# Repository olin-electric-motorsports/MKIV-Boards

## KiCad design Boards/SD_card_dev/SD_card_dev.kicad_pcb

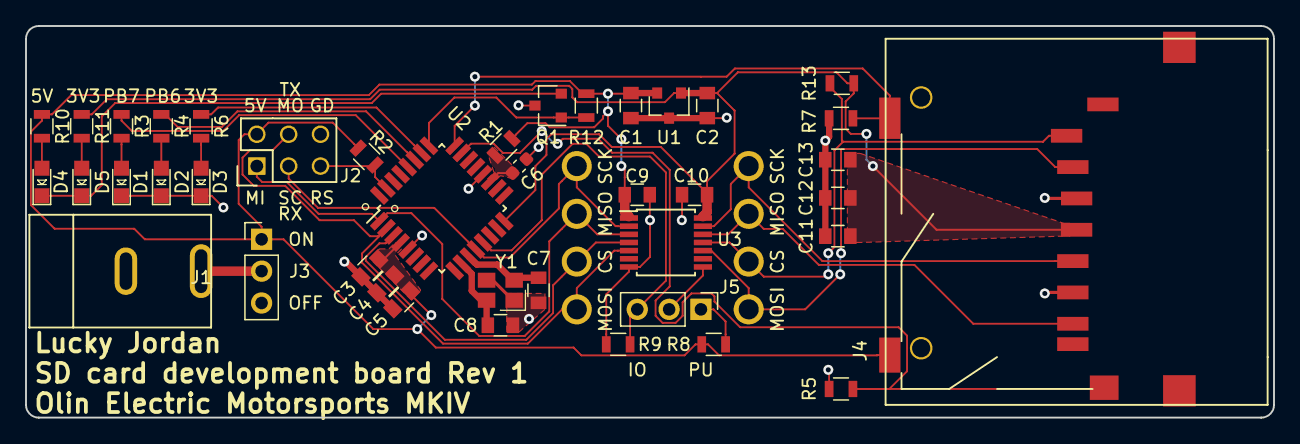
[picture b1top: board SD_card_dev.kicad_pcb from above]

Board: 2 copper layers, 99.6 x 31.2 mm, 49 parts (0 on the bottom side), 31 nets.

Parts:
C1, C2, C5, C9, C10, C13: C_0.1uF; C_0805_OEM
C3, C11: C_10uF; C_0805_OEM
C4, C12: C_1uF; C_0805_OEM
C6: C_100nF; C_0603_1608Metric
C7, C8: C_30pF; C_0805_OEM
CS: TP; tp_1.6mm
CS#2: TP; tp_1.6mm
D1, D2, D3, D4, D5: LED_0805; LED_0805_OEM
J1: Barrel_jack; barrel_jack_PJ-037A
J2: CONN_02X03; Pin_Header_Straight_2x03
J3, J5: CONN_01X03; Pin_Header_Straight_1x03_Pitch2.54mm
J4: SD_socket; sd_socket_molex_5009980900
MISO: TP; tp_1.6mm
MISO#2: TP; tp_1.6mm
MOSI: TP; tp_1.6mm
MOSI#2: TP; tp_1.6mm
Q1: SSM3K333R; SOT-23F
R1, R11: R_100; R_0805_OEM
R2, R5, R7, R8, R9, R12, R13: R_10K; R_0805_OEM
R3, R4, R6, R10: R_200; R_0805_OEM
SCK: TP; tp_1.6mm
SCK#2: TP; tp_1.6mm
U1: LM3480; SOT-23
U2: ATMEGA16M1; TQFP-32_7x7mm_Pitch0.8mm
U3: TXB0104; TSSOP-14_4.4x5mm_Pitch0.65mm
Y1: Crystal_SMD; Crystal_SMD_FA238

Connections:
+3V3: C2.1, C10.1, C11.1, C12.1, C13.1, J4.4, R11.1, R13.1, U1.1, U2.16, U3.14
+5V: C1.1, C3.1, C4.1, C5.1, C9.1, J2.2, J3.1, J4.10, R1.1, R2.1, R8.1, R10.1, R12.1, U1.2, U2.4, U3.1
/AVCC: C6.1, R1.2, U2.19
/Detect: J4.12, R7.1, U2.24
/LED1: R3.1, U2.28
/LED2: R4.1, U2.27
/LED3: R6.1, U2.26
/LED_drive: Q1.1, R12.2, U2.25
/MISO: J2.1, MISO.1, U2.1, U3.3
/MISO_3V3: J4.7, MISO#2.1, U3.12
/MOSI: J2.4, MOSI.1, U2.2, U3.5
/MOSI_3v3: J4.2, MOSI#2.1, U3.10
/OE: J5.2, U3.8
/OE_IO: J5.3, R9.1, U2.13
/Protect: J4.11, R5.1, U2.23
/RESET: J2.5, R2.2, U2.31
/SCK: J2.3, SCK.1, U2.12, U3.2
/SCK_3V3: J4.5, SCK#2.1, U3.13
/SS: CS.1, U2.3, U3.4
/SS_3V3: CS#2.1, J4.1, R13.2, U3.11
/XTAL1: C8.1, U2.10, Y1.3
/XTAL2: C7.1, U2.11, Y1.1
/cathode: D4.1, D5.1, Q1.2
GND: C1.2, C2.2, C3.2, C4.2, C5.2, C6.2, C7.2, C8.2, C9.2, C10.2, C11.2, C12.2, C13.2, D1.1, D2.1, D3.1, J1.2, J2.6, J4.3, J4.6, Q1.3, R5.2, R7.2, R9.2, U1.3, U2.5, U2.20, U3.7, Y1.2, Y1.4
unnamed: D1.2, R3.2
unnamed: D2.2, R4.2
unnamed: D3.2, R6.2
unnamed: D4.2, R10.2
unnamed: D5.2, R11.2
unnamed: J1.1, J3.2
unnamed: J5.1, R8.2

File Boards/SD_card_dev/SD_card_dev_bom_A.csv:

Component,Description,Part,References,Value,Footprint,Quantity Per PCB,Quantity Needed,Datasheet,MPN,MFN,PurchasingLink
1,"Capacitor, 0.1uF, 50V, 5%, 0805",C_0.1uF,C1 C2 C5 C9 C10 C13,C_0.1uF,C_0805_OEM,6,12,http://datasheets.avx.com/X7RDielectric.pdf,478-3352-1-ND,DK,https://www.digikey.com/products/en?keywords=478-3352-1-ND
2,"Capacitor, 0.1uF, 25V, 10%, 0603",C_100nF,C6,C_100nF,C_0603_1608Metric,1,2,http://www.samsungsem.com/kr/support/product-search/mlcc/CL1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,1276-6717-1-ND,DK,https://www.digikey.com/product-detail/en/samsung-electro-me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
3,"Capacitor, 10uF, 10V, 10%, 0805",C_10uF,C3 C11,C_10uF,C_0805_OEM,2,4,http://www.samsungsem.com/kr/support/product-search/mlcc/__i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,1276-1052-1-ND,DK,https://www.digikey.com/product-detail/en/samsung-electro-me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
4,"Capacitor, 1uF, 25V, 10%, 0805",C_1uF,C4 C12,C_1uF,C_0805_OEM,2,4,http://www.samsungsem.com/kr/support/product-search/mlcc/__i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,1276-2887-1-ND,DK,https://www.digikey.com/product-detail/en/samsung-electro-me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
5,"Capacitor, 30pF, 50V, 5%, 0805",C_30pF,C7 C8,C_30pF,C_0805_OEM,2,4,https://media.digikey.com/pdf/Data%20Sheets/Samsung%20PDFs/C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,1276-1130-1-ND,DK,https://www.digikey.com/product-detail/en/samsung-electro-me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
6,"LED, Green, 2.2V, 20mA, 0805",LED_0805,D1 D2 D3 D4 D5,LED_0805,LED_0805_OEM,5,10,http://www.osram-os.com/Graphics/XPic9/00078860_0.pdf,475-1410-1-ND,DK,https://www.digikey.com/products/en?keywords=475-1410-1-ND
7,"Barrel jack, 2.1x5.5mm, right angle, through hole",Barrel_jack,J1,Barrel_jack,barrel_jack_PJ-037A,1,2,https://www.cui.com/product/resource/pj-037a.pdf,CP-037A-ND,DK,https://www.digikey.com/product-detail/en/cui-inc/PJ-037A/CP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
8,"Connector header through hole 1x3 0.100"" (2.54mm)",CONN_01X03,J3 J5,CONN_01X03,Pin_Header_Straight_1x03_Pitch2.54mm,2,4,https://www.mouser.com/datasheet/2/181/M20-999-1218971.pdf,855-M20-9990346,Mouser,https://www.mouser.com/ProductDetail/Harwin/M20-9990346?qs=s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
9,"Connector header through hole 2x3 0.100"" (2.54mm)",CONN_02X03,J2,CONN_02X03,Pin_Header_Straight_2x03,1,2,http://portal.fciconnect.com/Comergent//fci/drawing/67996.pdf,609-3234-ND,DK,https://www.digikey.com/product-detail/en/amphenol-fci/67997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
10,SD card socket with detect switch,SD_socket,J4,SD_socket,sd_socket_molex_5009980900,1,2,https://www.molex.com/pdm_docs/sd/5009980900_sd.pdf,WM24032CT-ND,DK,https://www.digikey.com/product-detail/en/molex-llc/50099809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
11,"MOSFET, N-channel, 30V, 6A",SSM3K333R,Q1,SSM3K333R,SOT-23F,1,2,https://drive.google.com/drive/folders/0B-V-iZf33Y4GNzhDQTJZanJRbVk,SSM3K333RLFCT-ND,DK,https://www.digikey.com/product-detail/en/toshiba-semiconduc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
12,"Resistor, 100, 0.25W, 1%, 0805",R_100,R1 R11,R_100,R_0805_OEM,2,4,https://www.seielect.com/Catalog/SEI-rncp.pdf,RNCP0805FTD100RCT-ND,DK,https://www.digikey.com/products/en?keywords=RNCP0805FTD100RCT-ND
13,"Resistor, 10K, 0.25W, 1%, 0805",R_10K,R2 R5 R7 R8 R9 R12 R13,R_10K,R_0805_OEM,7,14,http://www.bourns.com/data/global/pdfs/CRS.pdf,CRS0805-FX-1002ELFCT-ND,DK,https://www.digikey.com/products/en?keywords=CRS0805-FX-1002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
14,"Resistor, 200, 0.125W, 5%, 0805",R_200,R3 R4 R6 R10,R_200,R_0805_OEM,4,8,https://www.seielect.com/Catalog/SEI-RMCF_RMCP.pdf,RMCF0805JT200RCT-ND,DK,https://www.digikey.com/products/en?keywords=RMCF0805JT200RCT-ND
15,"Microcontroller, 8-bit, 1KB RAM, 16KB Flash",ATMEGA16M1,U2,ATMEGA16M1,TQFP-32_7x7mm_Pitch0.8mm,1,2,http://ww1.microchip.com/downloads/en/DeviceDoc/Atmel-8209-8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,ATMEGA16M1-AU-ND,DK,https://www.digikey.com/product-detail/en/atmel/ATMEGA16M1-A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
16,"Linear regulator, 30V max input, 3.3V output, 100mA",LM3480,U1,LM3480,SOT-23,1,2,http://www.ti.com/lit/ds/symlink/lm3480.pdf,LM3480IM3-3.3CT-ND,DK,https://www.digikey.com/product-detail/en/texas-instruments/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
17,"Voltage level translator, 4-channel, bidirectional, TSSOP-14",TXB0104,U3,TXB0104,TSSOP-14_4.4x5mm_Pitch0.65mm,1,2,http://www.ti.com/lit/ds/symlink/txb0104.pdf,296-21929-1-ND,DK,https://www.digikey.com/product-detail/en/texas-instruments/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
18,CRYSTAL 16.0000MHZ 18PF SMD,Crystal_SMD,Y1,Crystal_SMD,Crystal_SMD_FA238,1,2,http://www.txccorp.com/download/products/quartz_crystals/201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,887-1125-1-ND,DK,https://www.digikey.com/product-detail/en/txc-corporation/7M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
,jumper,,,,,2,4,,S9341-ND,DK,https://www.digikey.com/product-detail/en/sullins-connector-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
,test point,,,,,8,16,,36-5006-ND,DK,
,wall wart,,,,,1,1,,993-1330-ND,DK,
,pocket avr programmer,,,,,1,1,,PGM-09825,sparkfun,https://www.sparkfun.com/products/9825
,uart to usb,,,,,1,1,,BOB-13830,sparkfun,https://www.sparkfun.com/products/13830
Component Groups:,18,,,,,,,,,,
Component Count:,41,,,,,,,,,,
Fitted Components:,41,,,,,,,,,,
Number of PCBs:,1,,,,,,,,,,
Total components:,41,,,,,,,,,,
Schematic Version:,A,,,,,,,,,,
Schematic Date:,2018-10-03,,,,,,,,,,
BoM Date:,Thu 04 Oct 2018 09:56:45 PM PDT,,,,,,,,,,
Schematic Source:,/home/lucky/Desktop/Formula/MKIV-Boards/Boards/SD_card_dev/SD_card_dev.sch,,,,,,,,,,
KiCad Version:,Eeschema 5.0.0-fee4fd1~66~ubuntu14.04.1,,,,,,,,,,

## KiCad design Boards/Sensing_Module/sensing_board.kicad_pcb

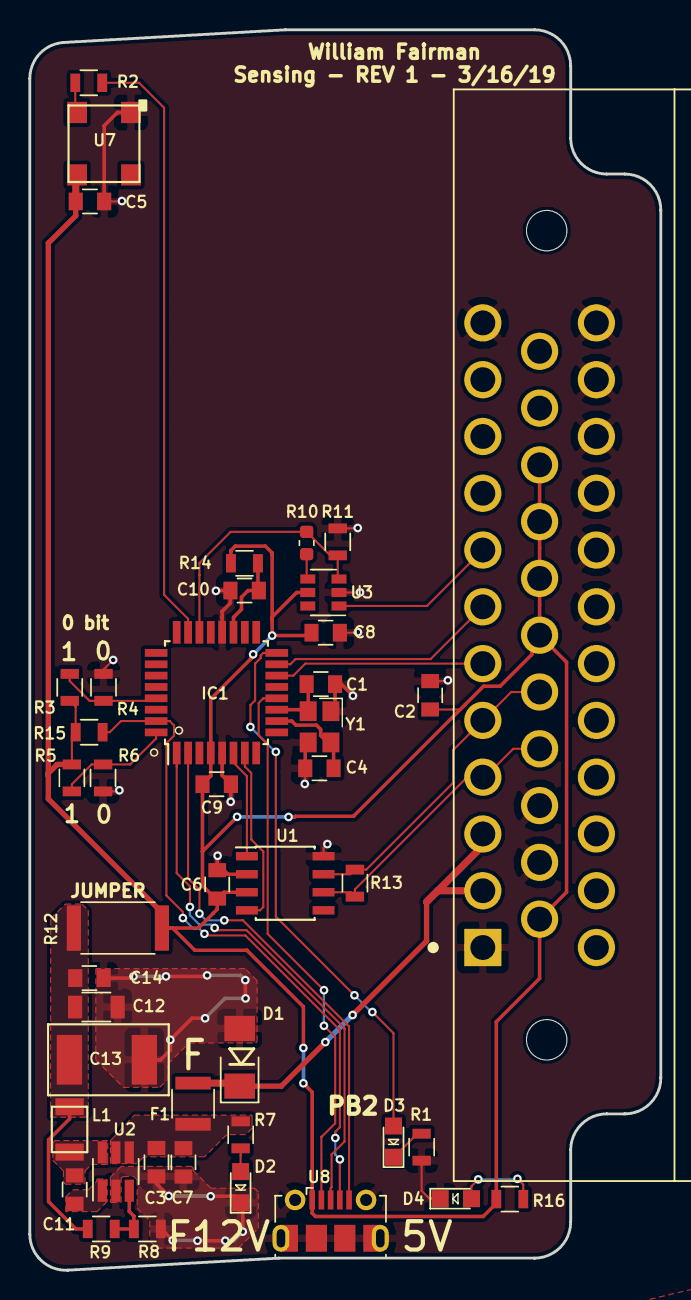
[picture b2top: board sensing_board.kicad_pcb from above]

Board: 2 copper layers, 44.5 x 87.4 mm, 44 parts (0 on the bottom side), 32 nets.

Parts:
C1, C4: C_30pF; C_0805_OEM
C2, C3, C5, C6, C8, C9, C11: C_0.1uF; C_0805_OEM
C7: C_2.2uF; C_0805_OEM
C10: C_100pF; C_0805_OEM
C12: C_22uF; C_1206_OEM
C13: C_33uF; C_1812
C14: C_47uF; C_0805_OEM
D1: D_Zener_18V; DO-214AA
D2, D3, D4: LED_0805; LED_0805_OEM
F1: F_500mA_16V; Fuse_1210
IC1: ATMEGA16M1; TQFP-32_7x7mm_Pitch0.8mm
J1: Ampseal_35_RA; TE_1-776180-1_35_RA
L1: L_100uH
R1, R2, R7, R16: R_200; R_0805_OEM
R3, R4, R5, R6, R11: R_1K; R_0805_OEM
R8: R_25K; R_0805_OEM
R9: R_100K; R_0805_OEM
R10: R_0; R_0603_1608Metric
R12: R_0_2512; R_2512_OEM
R13: R_120; R_0805_OEM
R14: R_100; R_0805_OEM
R15: R_10k; R_0805_OEM
U1: CAN_Transceiver; SOIC-8_3.9x4.9mm_Pitch1.27mm_OEM
U2: TPS560430YF; SOT-23-6_Handsoldering
U3: LMV341; SOT-23-6
U7: SK812; SK6812
U8: USB_MicroB; USB_Micro-B_Molex-105017-0001
Y1: Crystal_SMD; Crystal_SMD_FA238

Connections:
/12V: D1.1, F1.2, J1.2, J1.3
/BRAKETEMP: IC1.14, J1.6
/CANH: J1.5, J1.17, R13.1, U1.7
/CANL: J1.4, J1.16, R13.2, U1.6
/HSENSOR: IC1.15, J1.7
/MISO: IC1.1, U8.3
/MOSI: IC1.2, U8.5
/NEO_PIXEL: IC1.23, R2.1
/POT: J1.8, U3.1
/POT_SIGNAL: IC1.22, R10.2, R11.1, U3.3
/P_LED_1: D3.2, IC1.16
/RESET: IC1.31, R15.2, U8.4
/RXCAN: IC1.7, U1.4
/SCK: IC1.12, U8.2
/TXCAN: IC1.6, U1.1
GND: C1.2, C2.1, C3.2, C4.2, C5.1, C6.2, C7.2, C8.2, C9.2, C10.2, C12.2, C13.2, C14.2, D1.2, D2.1, D4.1, IC1.5, IC1.20, J1.1, J1.12, J1.14, J1.15, J1.30, J1.31, J1.32, J1.33, J1.34, J1.35, R1.2, R4.1, R6.2, R8.2, R11.2, U1.2, U1.8, U2.2, U3.2, U7.1, U8.6, Y1.2, Y1.4
unnamed: C1.1, IC1.11, Y1.1
unnamed: C3.1, C7.1, F1.1, R7.1, U2.4, U2.5
unnamed: C4.1, IC1.10, Y1.3
unnamed: C10.1, IC1.19, R14.2
unnamed: C11.1, U2.1
unnamed: C11.2, L1.1, U2.6
unnamed: C12.1, C13.1, C14.1, L1.2, R9.1, R12.2
unnamed: D2.2, R7.2
unnamed: D3.1, R1.1
unnamed: D4.2, R16.2
unnamed: IC1.29, R3.2, R4.2
unnamed: IC1.32, R5.2, R6.1
unnamed: R2.2, U7.2
unnamed: R8.1, R9.2, U2.3
unnamed: R10.1, U3.4
VCC: C2.2, C5.2, C6.1, C8.1, C9.1, IC1.4, J1.13, J1.18, J1.19, J1.20, J1.21, R3.1, R5.1, R12.1, R14.1, R15.1, R16.1, U1.3, U3.5, U7.3, U8.1

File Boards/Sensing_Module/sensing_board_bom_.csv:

Component,Description,Part,References,Value,Footprint,Quantity Per PCB,Datasheet,MFN,MPN,PurchasingLink,Package,Link,Digi-key Part Number,Purchasing Link
1,"b'Capacitor, 0.1uF, 50V, 5%, 0805'",b'C_0.1uF',b'C2 C3 C5 C6 C8 C9 C11',b'C_0.1uF',b'C_0805_OEM',b'7',b'http://datasheets.avx.com/X7RDielectric.pdf',b'DK Digi-Key',b'478-3352-1-ND',b'https://www.digikey.com/products/en?keywords=478-3352-1-ND',b'Value',b'',b'',b''
2,"b'Capacitor, 100pF, 50V, 5%, 0805'",b'C_100pF',b'C10',b'C_100pF',b'C_0805_OEM',b'1',b'https://content.kemet.com/datasheets/KEM_C1003_C0G_SMD.pdf',b'Digi-Key',b'399-1122-1-ND',b'https://www.digikey.com/product-detail/en/kemet/C0805C101J5G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,b'Value',b'',b'',b''
3,"b'Capacitor, 2.2uF, 10V, 10%, 0603'",b'C_2.2uF',b'C7',b'C_2.2uF',b'C_0603_1608Metric',b'1',b'http://www.yageo.com/documents/recent/UPY-GPHC_X5R_4V-to-50V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,b'DK',b'311-1451-1-ND',b'https://www.digikey.com/product-detail/en/yageo/CC0603KRX5R6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,b'',b'',b'',b''
4,"b'Capacitor, 22uF, 16V, 20%, 1206'",b'C_22uF',b'C12',b'C_22uF',b'C_1206_OEM',b'1',b'https://product.tdk.com/info/en/catalog/datasheets/mlcc_comm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,b'DK',b'445-11693-1-ND',b'https://www.digikey.com/product-detail/en/tdk-corporation/C3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,b'',b'',b'',b''
5,"b'Capacitor, 30pF, 50V, 5%, 0805'",b'C_30pF',b'C1 C4',b'C_30pF',b'C_0805_OEM',b'2',b'https://media.digikey.com/pdf/Data%20Sheets/Samsung%20PDFs/C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,b'Digi-Key',b'1276-1130-1-ND',b'https://www.digikey.com/product-detail/en/samsung-electro-me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,b'Value',b'',b'',b''
6,b'',b'C_33uF',b'C13',b'C_33uF',b'C_1812',b'1',b'https://product.tdk.com/info/en/catalog/datasheets/mlcc_comm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,b'C4532X7R1C336M250KC',b'445-3924-1-ND',b'https://www.digikey.com/product-detail/en/tdk-corporation/C4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,b'',b'',b'',b''
7,"b'Capacitor, 47uF, 6.3V, 20%, 0805'",b'C_47uF',b'C14',b'C_47uF',b'C_0805_OEM',b'1',b'http://www.samsungsem.com/kr/support/product-search/mlcc/__i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,b'DK',b'1276-6467-1-ND',b'https://www.digikey.com/product-detail/en/samsung-electro-me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,b'',b'',b'',b''
8,"b'Diode, Zener, 18V, 5W, 5%'",b'D_Zener_18V',b'D1',b'D_Zener_18V',b'DO-214AA',b'1',b'http://www.mccsemi.com/up_pdf/SMBJ5338B-SMBJ5388B(SMB).pdf',b'DK',b'SMBJ5355B-TPMSCT-ND',b'https://www.digikey.com/products/en?keywords=SMBJ5355B-TPMSCT-ND',b'',b'',b'',b''
9,"b'LED, Green, 2.2V, 20mA, 0805'",b'LED_0805',b'D2 D3 D4',b'LED_0805',b'LED_0805_OEM',b'3',b'http://www.osram-os.com/Graphics/XPic9/00078860_0.pdf',b'DK',b'475-1410-1-ND',b'https://www.digikey.com/products/en?keywords=475-1410-1-ND',b'',b'',b'',b''
10,"b'Fuse, PTC, 500mA, 16V, 1210'",b'F_500mA_16V',b'F1',b'F_500mA_16V',b'Fuse_1210',b'1',b'https://belfuse.com/resources/CircuitProtection/datasheets/0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,b'DK',b'507-1786-1-ND',b'https://www.digikey.com/product-detail/en/bel-fuse-inc/0ZCH0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,b'',b'',b'',b''
11,"b'Microcontroller, 8-bit, 1KB RAM, 16KB Flash'",b'ATMEGA16M1',b'IC1',b'ATMEGA16M1',b'TQFP-32_7x7mm_Pitch0.8mm',b'1',b'http://www.atmel.com/Images/Atmel-8209-8-bit%20AVR%20ATmega1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,b'Digi-Key',b'ATMEGA16M1-AU-ND',b'https://www.digikey.com/product-detail/en/atmel/ATMEGA16M1-A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,b'Value',b'',b'',b''
12,b'Ampseal connector 35 pin right angle',b'Ampseal_35_RA',b'J1',b'Ampseal_35_RA',b'TE_1-776180-1_35_RA',b'1',b'http://www.te.com/commerce/DocumentDelivery/DDEController?Ac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,b'TE',b'776180-1',b'http://www.te.com/usa-en/product-776180-1.html',b'',b'',b'',b''
13,b'',b'L_100uH',b'L1',b'L_100uH',b'L_100uH',b'1',b'https://product.tdk.com/info/en/catalog/datasheets/inductor_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,b'Digikey',b'445-15759-1-ND',b'',b'',b'https://www.digikey.com/product-detail/en/tdk-corporation/NL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,b'',b''
14,"b'Resistor, 0 ohm jumper, 0.1W, 0603'",b'R_0',b'R10',b'R_0',b'R_0603_1608Metric',b'1',b'http://industrial.panasonic.com/www-cgi/jvcr13pz.cgi?E+PZ+3+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,b'DK',b'P0.0GCT-ND',b'https://www.digikey.com/product-detail/en/panasonic-electron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,b'',b'',b'',b''
15,"b'Resistor, 0 ohm jumper, 3W, 2512'",b'R_0_2512',b'R12',b'R_0_2512',b'R_2512_OEM',b'1',b'http://www.te.com/commerce/DocumentDelivery/DDEController?Ac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,b'DK',b'A121322CT-ND',b'https://www.digikey.com/products/en?keywords=A121322CT-ND',b'',b'',b'',b''
16,"b'Resistor, 100, 0.25W, 1%, 0805'",b'R_100',b'R14',b'R_100',b'R_0805_OEM',b'1',b'https://www.seielect.com/Catalog/SEI-rncp.pdf',b'Digi-Key',b'RNCP0805FTD100RCT-ND',b'https://www.digikey.com/products/en?keywords=RNCP0805FTD100RCT-ND',b'Value',b'',b'',b''
17,"b'Resistor, 100K, 0.125W, 1%, 0805'",b'R_100K',b'R9',b'R_100K',b'R_0805_OEM',b'1',b'https://industrial.panasonic.com/cdbs/www-data/pdf/RDA0000/A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,b'DK',b'P100KCCT-ND',b'https://www.digikey.com/product-detail/en/panasonic-electron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,b'',b'',b'',b''
18,"b'Resistor, 10K, 0.25W, 1%, 0805'",b'R_10K',b'R15',b'R_10k',b'R_0805_OEM',b'1',b'http://www.bourns.com/data/global/pdfs/CRS.pdf',b'Digi-Key',b'CRS0805-FX-1002ELFCT-ND',b'https://www.digikey.com/products/en?keywords=CRS0805-FX-1002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,b'Value',b'',b'',b''
19,"b'Resistor, 120, 0.125W, 1%, 0805'",b'R_120',b'R13',b'R_120',b'R_0805_OEM',b'1',b'https://www.mouser.com/datasheet/2/315/AOA0000C304-1149620.pdf',b'DK',b'667-ERJ-6ENF1200V',b'https://www.mouser.com/ProductDetail/Panasonic-Industrial-De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,b'',b'',b'',b''
20,"b'Resistor, 1K, 0.25W, 1%, 0805'",b'R_1K',b'R3 R4 R5 R6 R11',b'R_1K',b'R_0805_OEM',b'5',b'https://www.seielect.com/Catalog/SEI-rncp.pdf',b'DK',b'RNCP0805FTD1K00CT-ND',b'https://www.digikey.com/products/en?keywords=RNCP0805FTD1K00CT-ND',b'',b'',b'',b''
21,"b'Resistor, 200, 0.125W, 5%, 0805'",b'R_200',b'R1 R2 R7 R16',b'R_200',b'R_0805_OEM',b'4',b'https://www.seielect.com/Catalog/SEI-RMCF_RMCP.pdf',b'DK',b'RMCF0805JT200RCT-ND',b'https://www.digikey.com/products/en?keywords=RMCF0805JT200RCT-ND',b'',b'',b'',b''
22,b'',b'R_25K',b'R8',b'R_25K',b'R_0805_OEM',b'1',b'https://www.te.com/commerce/DocumentDelivery/DDEController?A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,b'A124124CT-ND',b'',b'https://www.digikey.com/product-detail/en/te-connectivity-pa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,b'',b'',b'CPF-A-0805B25KE',b''
23,"b'High speed CAN transceiver, 1Mb/s'",b'MCP2561-E_SN',b'U1',b'CAN_Transceiver',b'SOIC-8_3.9x4.9mm_Pitch1.27mm_OEM',b'1',b'http://www.microchip.com/mymicrochip/filehandler.aspx?ddocna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,b'Digi-Key',b'MCP2561-E/SN-ND',b'https://www.digikey.com/products/en?keywords=mcp2561-e%2Fsn',b'Value',b'',b'',b''
24,"b'Op-amp, general purpose'",b'LMV341',b'U3',b'LMV341',b'SOT-23-6',b'1',b'http://www.ti.com/lit/ds/symlink/lmv341.pdf',b'DK',b'296-17843-1-ND',b'https://www.digikey.com/product-detail/en/texas-instruments/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,b'',b'',b'',b''
25,b'',b'SK812',b'U7',b'SK812',b'SK6812',b'1',b'https://cdn-shop.adafruit.com/product-files/1138/SK6812+LED+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,b'',b'',b'https://www.digikey.com/product-detail/en/adafruit-industrie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,b'',b'',b'',b''
26,b'',b'TPS560430YF',b'U2',b'TPS560430YF',b'SOT-23-6_Handsoldering',b'1',b'http://www.ti.com/lit/ds/symlink/tps560430.pdf',b'TPS560430YFDBVR-ND',b'TPS560430YFDBVR',b'',b'',b'',b'',b'https://www.digikey.com/product-detail/en/texas-instruments/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
27,b'',b'USB_MicroB',b'U8',b'USB_MicroB',b'USB_Micro-B_Molex-105017-0001',b'1',b'https://www.molex.com/pdm_docs/sd/1050170001_sd.pdf',b'DK',b'WM1399CT-ND',b'https://www.digikey.com/product-detail/en/molex-llc/10501700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,b'',b'',b'',b''
28,b'CRYSTAL 16.0000MHZ 18PF SMD',b'Crystal_SMD',b'Y1',b'Crystal_SMD',b'Crystal_SMD_FA238',b'1',b'https://support.epson.biz/td/api/doc_check.php?dl=brief_FA-2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,b'Digi-Key',b'SER3686CT-ND',b'https://www.digikey.com/products/en?keywords=SER3686CT-ND',b'Value',b'',b'',b''





Component Groups:,28
Component Count:,44
Fitted Components:,44
Number of PCBs:,1
Total components:,44
Schematic Version:,
Schematic Date:,
BoM Date:,b'Sat 30 Mar 2019 09:28:12 AM EDT'
Schematic Source:,b'/home/william/Desktop/MKIV-Boards/Boards/Sensing_Module/sensing_board.sch'
KiCad Version:,b'Eeschema 5.0.0-fee4fd1~66~ubuntu16.04.1'

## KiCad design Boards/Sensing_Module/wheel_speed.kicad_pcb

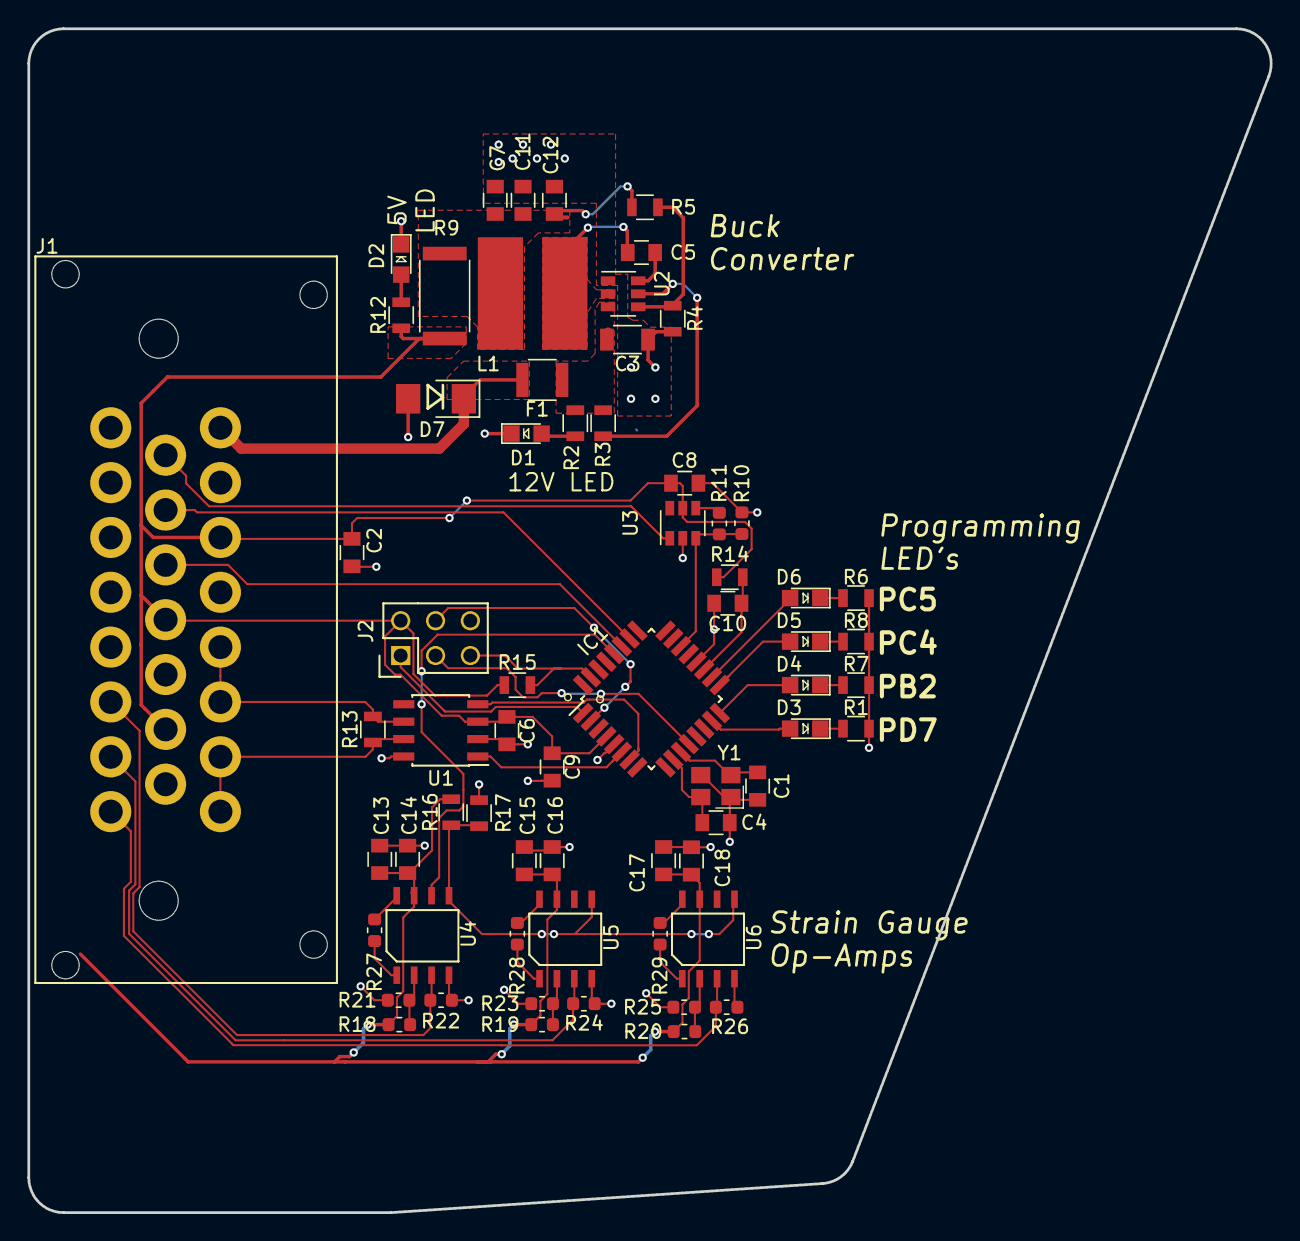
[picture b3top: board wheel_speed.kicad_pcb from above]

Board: 2 copper layers, 90.6 x 86.4 mm, 66 parts (0 on the bottom side), 51 nets.

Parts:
C1, C4: C_30pF; C_0805_OEM
C2, C5, C6, C8, C9, C12, C14, C16, C18: C_0.1uF; C_0805_OEM
C3: C_22uF; C_1206_OEM
C7: C_47uF; C_0805_OEM
C10: C_100pF; C_0805_OEM
C11: C_1uF; C_0805_OEM
C13, C15, C17: C_10uF; C_0805_OEM
D1, D2, D3, D4, D5, D6: LED_0805; LED_0805_OEM
D7: D_Zener_18V; DO-214AA
F1: 500mA; Fuse_1210
IC1: ATMEGA16M1; TQFP-32_7x7mm_Pitch0.8mm
J1: Ampseal_23_RA; Ampseal_23
J2: CONN_02X03; Pin_Header_Straight_2x03
L1: L_4.7uH; 4.7uH_Inductor_OEM
R1, R6, R7, R8, R12: R_200; R_0805_OEM
R2: R_1k; R_0805_OEM
R3, R4, R15: R_10k; R_0805_OEM
R5: R_51.1k; R_0805_OEM
R9: R_0_Jumper; R_2512_OEM
R10, R11, R18, R19, R20, R21, R22, R23, R24, R25, R26, R27, R28, R29: R_0; R_0603_1608Metric
R13: R_120; R_0805_OEM
R14: R_100; R_0805_OEM
R16, R17: R_10K; R_0805_OEM
U1: CAN_Transceiver; SOIC-8_3.9x4.9mm_Pitch1.27mm_OEM
U2: TPS561201; SOT-23-6_OEM
U3: LMV341; SOT-23-6
U4, U5, U6: AD623; AD623_SOIC-8
Y1: Crystal_SMD; Crystal_SMD_FA238

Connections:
+12V: D7.1, F1.1, J1.1
/12V_Fused: C3.1, F1.2, R2.1, R3.1, U2.3
/BRAKETEMP: IC1.27, J1.11
/CANH: J1.7, J1.8, R13.1, U1.7
/CANL: J1.5, J1.6, R13.2, U1.6
/HSENSOR: IC1.26, J1.10
/MISO: IC1.1, J2.1
/MOSI: IC1.2, J2.4
/POT: J1.9, U3.1
/POT_SIGNAL: IC1.22, R10.1, R11.2, U3.3
/P_LED_1: D3.2, IC1.15
/P_LED_2: D4.2, IC1.16
/P_LED_3: D5.2, IC1.17
/P_LED_4: D6.2, IC1.18
/RESET: IC1.31, J2.5, R15.2
/RXCAN: IC1.7, U1.4
/SCK: IC1.12, J2.3
/Suspension Strain Testing/2.5V: R16.2, R17.1, U4.5, U5.5, U6.5
/TXCAN: IC1.6, U1.1
GND: C1.2, C2.1, C3.2, C4.2, C6.2, C7.2, C8.2, C9.2, C10.2, C11.2, C12.2, C13.1, C14.1, C15.1, C16.1, C17.1, C18.1, D1.1, D2.1, D7.2, IC1.5, IC1.20, J1.2, J1.4, J1.13, J1.15, J2.6, R1.2, R4.2, R6.2, R7.2, R8.2, R10.2, R17.2, R21.1, R22.1, R23.1, R24.1, R25.1, R26.1, U1.2, U1.8, U2.1, U3.2, U4.4, U5.4, U6.4, Y1.2, Y1.4
unnamed: C1.1, IC1.11, Y1.1
unnamed: C4.1, IC1.10, Y1.3
unnamed: C5.1, U2.6
unnamed: C5.2, L1.1, U2.2
unnamed: C10.1, IC1.19, R14.2
unnamed: C7.1, C11.1, C12.1, L1.2, R5.2, R9.2
unnamed: D1.2, R2.2
unnamed: D2.2, R12.2
unnamed: D3.1, R1.1
unnamed: D4.1, R7.1
unnamed: D5.1, R8.1
unnamed: D6.1, R6.1
unnamed: R3.2, U2.5
unnamed: R4.1, R5.1, U2.4
unnamed: R11.1, U3.4
unnamed: R18.1, R21.2, U4.2
unnamed: R19.1, R23.2, U5.2
unnamed: R20.1, R25.2, U6.2
unnamed: R27.1, U4.8
unnamed: R27.2, U4.1
unnamed: R28.1, U5.8
unnamed: R28.2, U5.1
unnamed: R29.1, U6.8
unnamed: R29.2, U6.1
VCC: C2.2, C6.1, C8.1, C9.1, C13.2, C14.2, C15.2, C16.2, C17.2, C18.2, IC1.4, J1.3, J1.12, J1.14, J2.2, R9.1, R12.1, R14.1, R15.1, R16.1, R18.2, R19.2, R20.2, U1.3, U3.5, U4.7, U5.7, U6.7
gauge1.1in: J1.21, R22.2, U4.3
gauge1.1out: IC1.28, U4.6
gauge1.2in: J1.22, R24.2, U5.3
gauge1.2out: IC1.13, U5.6
gauge1.3in: J1.23, R26.2, U6.3
gauge1.3out: IC1.14, U6.6

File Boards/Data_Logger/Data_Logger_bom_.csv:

Component,Description,Part,References,Value,Footprint,Quantity Per PCB,Datasheet,Package,MPN,MFN,PurchasingLink,Purchasing Link
1,"Capacitor, 0.1uF, 50V, 5%, 0805",C_0.1uF,C1 C4 C5 C9 C10 C12 C15 C16,C_0.1uF,C_0805_OEM,8,http://datasheets.avx.com/X7RDielectric.pdf,Value,478-3352-1-ND,Digi-Key DK,https://www.digikey.com/products/en?keywords=478-3352-1-ND,
2,"Capacitor, 100pF, 50V, 5%, 0805",C_100pF,C2,C_100pF,C_0805_OEM,1,https://content.kemet.com/datasheets/KEM_C1003_C0G_SMD.pdf,Value,399-1122-1-ND,Digi-Key,https://www.digikey.com/product-detail/en/kemet/C0805C101J5G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,
3,"Capacitor, 10uF, 10V, 10%, 0805",C_10uF,C13,C_10uF,C_0805_OEM,1,http://www.samsungsem.com/kr/support/product-search/mlcc/__i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,,1276-1052-1-ND,DK,https://www.digikey.com/product-detail/en/samsung-electro-me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,
4,"Capacitor, 1uF, 25V, 10%, 0805",C_1uF,C11 C14,C_1uF,C_0805_OEM,2,http://datasheets.avx.com/X7RDielectric.pdf,Value,478-10487-1-ND 1276-2887-1-ND,Digi-Key DK,https://www.digikey.com/product-detail/en/avx-corporation/08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 https://www.digikey.com/product-detail/en/samsung-electro-me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,
5,"Capacitor, 22uF, 16V, 20%, 1206",C_22uF,C3,C_22uF,C_1206_OEM,1,http://www.samsungsem.com/kr/support/product-search/mlcc/__i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,Value,1276-2725-1-ND,Digi-Key,https://www.digikey.com/products/en?keywords=1276-2725-1-ND,
6,"Capacitor, 30pF, 50V, 5%, 0805",C_30pF,C6 C8,C_30pF,C_0805_OEM,2,https://media.digikey.com/pdf/Data%20Sheets/Samsung%20PDFs/C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,Value,1276-1130-1-ND,Digi-Key,https://www.digikey.com/product-detail/en/samsung-electro-me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,
7,"Capacitor, 47uF, 6.3V, 20%, 0805",C_47uF,C7,C_47uF,C_0805_OEM,1,http://www.yuden.co.jp/productdata/catalog/en/mlcc_all_e.pdf,Value,587-4280-1-ND,Digi-Key,https://www.digikey.com/product-detail/en/taiyo-yuden/JMK212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,
8,"Diode, Zener, 18V, 5W, 5%",D_Zener_18V,D7,D_Zener_18V,DO-214AA,1,http://www.mccsemi.com/up_pdf/SMBJ5338B-SMBJ5388B(SMB).pdf,DO-214AA (SMB),SMBJ5355B-TPMSCT-ND,Digi-Key,https://www.digikey.com/products/en?keywords=SMBJ5355B-TPMSCT-ND,
9,"LED, Green, 2.2V, 20mA, 0805",LED_0805,D1 D2 D3 D4 D5,LED_0805,LED_0805_OEM,5,http://www.osram-os.com/Graphics/XPic9/00078860_0.pdf,Value,475-1410-1-ND,Digi-Key DK,https://www.digikey.com/products/en?keywords=475-1410-1-ND,
10,"Fuse, PTC, 500mA, 16V, 1210",F_500mA_16V,F1,500mA,Fuse_1210,1,https://belfuse.com/resources/CircuitProtection/datasheets/0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,Value,507-1786-1-ND,Digi-Key,https://www.digikey.com/product-detail/en/bel-fuse-inc/0ZCH0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,
11,"Microcontroller, 8-bit, 1KB RAM, 16KB Flash",ATMEGA16M1,IC1,ATMEGA16M1,TQFP-32_7x7mm_Pitch0.8mm,1,http://www.atmel.com/Images/Atmel-8209-8-bit%20AVR%20ATmega1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,Value,ATMEGA16M1-AU-ND,Digi-Key,https://www.digikey.com/product-detail/en/atmel/ATMEGA16M1-A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,
12,"Connector header through hole 2x3 0.100"" (2.54mm)",CONN_02X03,J4,CONN_02X03,Pin_Header_Straight_2x03,1,http://portal.fciconnect.com/Comergent//fci/drawing/67996.pdf,Value,609-3234-ND,Digi-Key,https://www.digikey.com/product-detail/en/amphenol-fci/67997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,
13,"Generic connector, single row, 01x03, script generated (kicad-library-utils/schlib/autogen/connector/)",Conn_01x03,J2,Conn_01x03,PinHeader_1x03_P2.54mm_Vertical,1,~,,,,,
14,Micro-MaTch connector 20 pin female right angle,MM_F_RA_20,J3,MM_F_RA_20,micromatch_female_ra_20,1,http://www.te.com/commerce/DocumentDelivery/DDEController?Ac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,,2-338070-0,TE,http://www.te.com/usa-en/product-2-338070-0.html,
15,SD card socket with detect switch,SD_socket,J1,SD_socket,sd_socket_molex_5009980900,1,https://www.molex.com/pdm_docs/sd/5009980900_sd.pdf,,WM24032CT-ND,DK,https://www.digikey.com/product-detail/en/molex-llc/50099809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,
16,"Inductor, 4.7uH, 4.4A, 25mOhm, 20%",L_4.7uH,L1,L_4.7uH,4.7uH_Inductor_OEM,1,https://product.tdk.com/info/en/documents/wdcatalog/withdraw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,Value,445-6583-1-ND,Digi-Key,https://www.digikey.com/product-detail/en/tdk-corporation/VL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,
17,"Resistor, 0 ohm jumper, 0.1W, 0603",R_0,R9,R_0_Jumper,R_2512_OEM,1,http://www.te.com/commerce/DocumentDelivery/DDEController?Ac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,Value,A121322CT-ND,Digi-Key,https://www.digikey.com/products/en?keywords=A121322CT-ND,
18,"Resistor, 100, 0.25W, 1%, 0805",R_100,R1,R_100,R_0805_OEM,1,https://www.seielect.com/Catalog/SEI-rncp.pdf,Value,RNCP0805FTD100RCT-ND,Digi-Key,https://www.digikey.com/products/en?keywords=RNCP0805FTD100RCT-ND,
19,"Resistor, 10K, 0.25W, 1%, 0805",R_10K,R8 R13 R14 R15 R16 R17,R_10k,R_0805_OEM,6,http://www.bourns.com/data/global/pdfs/CRS.pdf,Value,CRS0805-FX-1002ELFCT-ND,Digi-Key DK,https://www.digikey.com/products/en?keywords=CRS0805-FX-1002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,
20,"Resistor, 10K, 5W, 1%, Axial",R_10K_HV,R3 R4,R_10k,R_0805_OEM,2,http://www.bourns.com/data/global/pdfs/CRS.pdf,Value,CRS0805-FX-1002ELFCT-ND,Digi-Key,https://www.digikey.com/products/en?keywords=CRS0805-FX-1002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,
21,"Resistor, 120, 0.125W, 1%, 0805",R_120,R7,R_120,R_0805_OEM,1,https://www.mouser.com/datasheet/2/315/AOA0000C304-1149620.pdf,,667-ERJ-6ENF1200V,DK,https://www.mouser.com/ProductDetail/Panasonic-Industrial-De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,
22,"Resistor, 1K, 0.25W, 1%, 0805",R_1K,R2,R_1k,R_0805_OEM,1,https://www.seielect.com/Catalog/SEI-rncp.pdf,Value,RNCP0805FTD1K00CT-ND,Digi-Key,https://www.digikey.com/products/en?keywords=RNCP0805FTD1K00CT-ND,
23,"Resistor, 200, 0.125W, 5%, 0805",R_200,R6 R10 R11 R12 R18 R19,R_200,R_0805_OEM,6,https://www.seielect.com/Catalog/SEI-RMCF_RMCP.pdf,Value,RMCF0805JT200RCT-ND,DK Digi-Key,https://www.digikey.com/products/en?keywords=RMCF0805JT200RCT-ND,
24,"Resistor, 51.1K, 0.125W, 1%, 0805",R_51.1K,R5,R_51.1k,R_0805_OEM,1,http://www.yageo.com.tw/exep/pages/download/literatures/PYu-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,Value,311-51.1KCRCT-ND,Digi-Key,https://www.digikey.com/products/en?keywords=311-51.1KCRCT-ND,
25,Slider Switch,MHSS1105,S1,MHSS1105,MHSS1105,1,https://www.apem.com/us/index.php?controller=attachment&id_a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,,679-1849-ND,APEM Inc.,,https://www.digikey.com/product-detail/en/apem-inc/MHSS1105/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
26,"High speed CAN transceiver, 1Mb/s",MCP2561-E_SN,U1,CAN_Transceiver,SOIC-8_3.9x4.9mm_Pitch1.27mm_OEM,1,http://www.microchip.com/mymicrochip/filehandler.aspx?ddocna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,Value,MCP2561-E/SN-ND,Digi-Key,https://www.digikey.com/products/en?keywords=mcp2561-e%2Fsn,
27,"Buck converter, 4.5-17V input, adj 0.76-7V output, 1A, 580kHz",TPS561201,U2,TPS561201,SOT-23-6_OEM,1,http://www.ti.com/lit/ds/symlink/tps561201.pdf,Value,TPS561201,Digi-Key,https://www.digikey.com/products/en?keywords=296-46928-1-ND,
28,"Voltage level translator, 4-channel, bidirectional, TSSOP-14",TXB0104,U3,TXB0104,TSSOP-14_4.4x5mm_P0.65mm,1,http://www.ti.com/lit/ds/symlink/txb0104.pdf,,296-21929-1-ND,DK,https://www.digikey.com/product-detail/en/texas-instruments/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,
29,CRYSTAL 16.0000MHZ 18PF SMD,Crystal_SMD,Y1,Crystal_SMD,Crystal_SMD_FA238,1,https://support.epson.biz/td/api/doc_check.php?dl=brief_FA-2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,Value,SER3686CT-ND,Digi-Key,https://www.digikey.com/products/en?keywords=SER3686CT-ND,





Component Groups:,29
Component Count:,53
Fitted Components:,53
Number of PCBs:,1
Total components:,53
Schematic Version:,
Schematic Date:,
BoM Date:,Thu 31 Jan 2019 08:48:02 PM EST
Schematic Source:,/home/thomas/Documents/Formula/MKIV-Boards/Boards/Data_Logger/Data_Logger.sch
KiCad Version:,Eeschema 5.0.2-bee76a0~70~ubuntu18.04.1
